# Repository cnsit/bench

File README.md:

# bench
An ideal bench design.
- [ ] Printer
- [ ] Copier & Scanner
- [ ] 3D Printer
- [ ] CNC
- [ ] Laser Cutter
- [ ] Power Supplies x2
- [ ] FT-991
- [ ] PC
- [ ] Mac
- [ ] Projector
- [ ] Stereo Audio
- [ ] 27 inch monitor
- [ ] Welding Station
- [ ] Tex 2465
- [ ] Curve Tracer
- [ ] Signal Generator x2
- [ ] Multimeter Holder x4
- [ ] Coax Cable holder
- [ ] No shadow lights
- [ ] Switch with serve nodes
- [ ] Antenna switch
- [ ] Optical

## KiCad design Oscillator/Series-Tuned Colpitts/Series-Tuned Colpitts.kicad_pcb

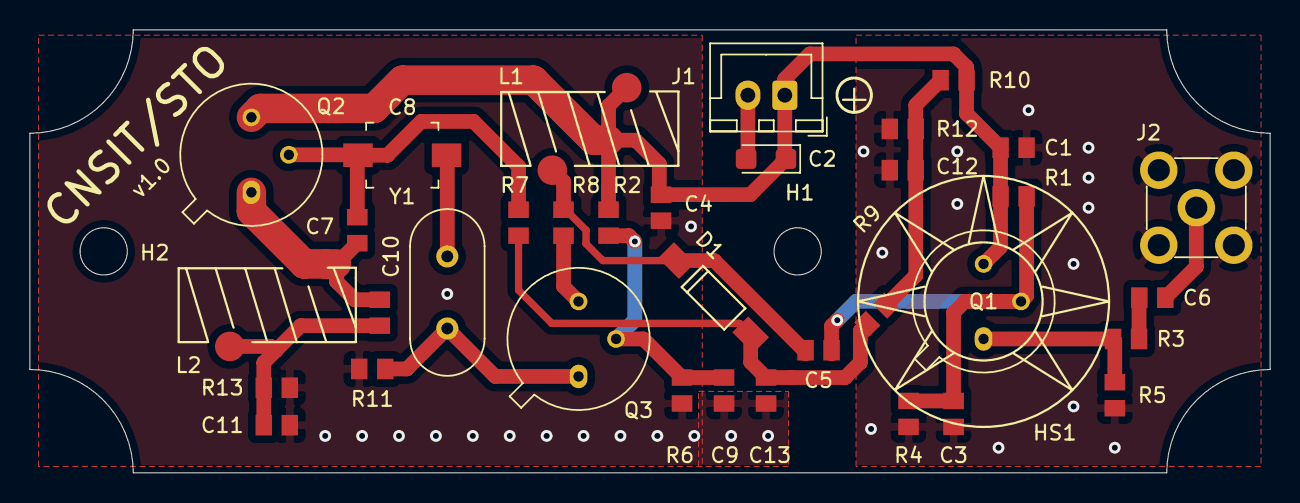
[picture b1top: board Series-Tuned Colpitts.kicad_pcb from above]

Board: 2 copper layers, 84.0 x 30.0 mm, 38 parts (0 on the bottom side), 16 nets.

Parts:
C1, C4, C6, C9, C11, C12, C13: 0.1u; C_0805_2012Metric
C2: 10u; CP_EIA-3216-10_Kemet-I
C3: 470p; C_0805_2012Metric
C5: 110p; C_0805_2012Metric
C7: 390p; C_0805_2012Metric
C8: 30p; C_Trimmer_Murata_TZB4-B
C10: 510p; C_0805_2012Metric
D1: 1N60; SMT_DIODE
H1, H2: MountingHole; MountingHole_3.2mm_M3
HS1: Heatsink; TO_39_Crown
J1: PWR; XH-A_1x02_Vertical_Power_In
J2: Out; SMA_Amphenol_901-144_Vertical
L1, L2: 4.3u; L_3743
Q1, Q2, Q3: 2N2219; TO-39-3
R1, R4: 10k; R_0805_2012Metric
R2: 6.8k; R_0805_2012Metric
R3: 470; R_0805_2012Metric
R5, R12, R13: 1k; R_0805_2012Metric
R6: 2.7k; R_0805_2012Metric
R7: 20k; R_0805_2012Metric
R8: 220; R_0805_2012Metric
R9: 33k; R_0805_2012Metric
R10: 1.5k; R_0805_2012Metric
R11: 270; R_0805_2012Metric
Y1: Crystal; Crystal_HC49-U_Vertical

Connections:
GND: C1.2, C2.2, C3.1, C4.2, C9.1, C11.2, C12.2, C13.2, J1.2, J2.2, R4.2, R5.2, R6.1, R11.2, R12.2, R13.2
unnamed: C1.1, C2.1, C4.1, J1.1, L1.1, Q1.3, Q2.3, R1.1, R2.1, R10.1
unnamed: C3.2, C5.1, Q1.2, R1.2, R4.1
unnamed: C5.2, D1.1, L1.2, R8.1
unnamed: C6.1, J2.1
unnamed: C6.2, R3.1
unnamed: C7.1, C8.1, Q2.2, R7.1
unnamed: C8.2, Y1.1
unnamed: C9.2, Q3.2, R2.2, R6.2
unnamed: C7.2, C10.1, L2.1, Q2.1
unnamed: C10.2, C11.1, L2.2, R13.1
unnamed: C12.1, R9.1, R10.2, R12.1
unnamed: C13.1, D1.2, R7.2, R9.2
unnamed: Q1.1, R3.2, R5.1
unnamed: Q3.1, R11.1, Y1.2
unnamed: Q3.3, R8.2

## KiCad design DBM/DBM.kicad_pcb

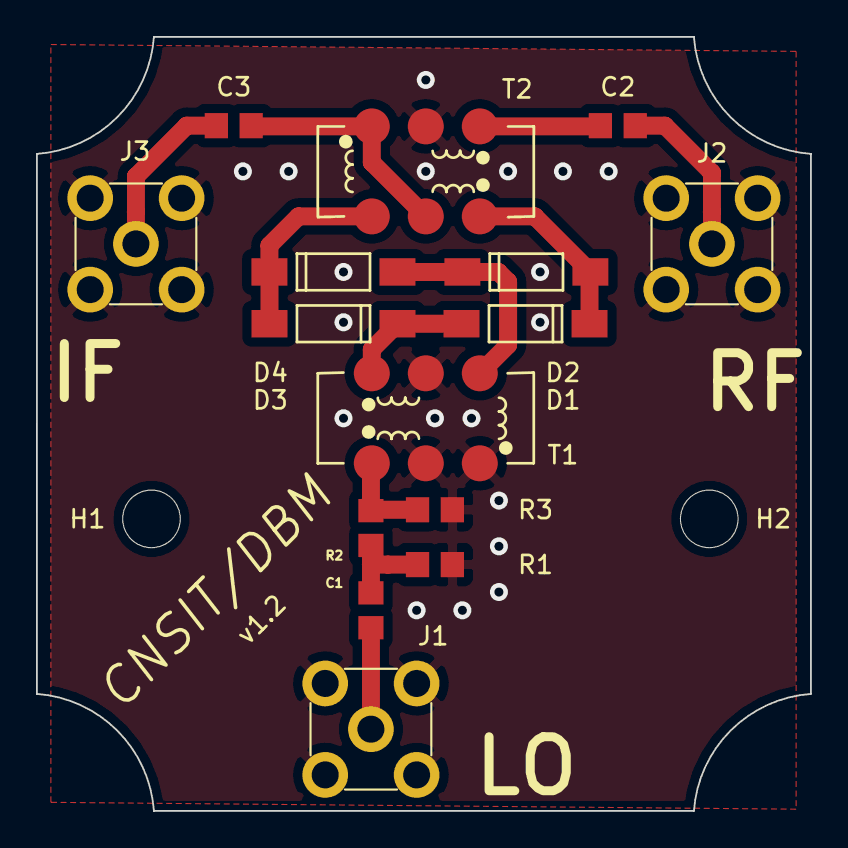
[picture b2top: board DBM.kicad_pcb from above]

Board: 2 copper layers, 43.0 x 43.0 mm, 17 parts (0 on the bottom side), 12 nets.

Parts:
C1, C2, C3: 0.1u; C_0805_2012Metric_Pad1.29x1.40mm_HandSolder
D1, D2, D3, D4: 1N60; SMT_DIODE
H1, H2: MountingHole; MountingHole_3.2mm_M3
J1: LO; SMA_Amphenol_901-144_Vertical
J2: RF; SMA_Amphenol_901-144_Vertical
J3: IF; SMA_Amphenol_901-144_Vertical
R1, R3: 150; R_0805_2012Metric_Pad1.29x1.40mm_HandSolder
R2: 37; R_0805_2012Metric_Pad1.29x1.40mm_HandSolder
T1, T2: T_3743; T_3743_6

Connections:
GNDA: J1.2, J2.2, J3.2, R1.2, R3.2, T1.2, T1.4, T1.5, T2.2
unnamed: C1.1, R1.1, R2.2
unnamed: C1.2, J1.1
unnamed: C2.1, T2.1
unnamed: C2.2, J2.1
unnamed: C3.1, J3.1
unnamed: C3.2, T2.4, T2.5
unnamed: D1.1, D2.2, T2.3
unnamed: D1.2, D3.1, T1.3
unnamed: D2.1, D4.2, T1.6
unnamed: D3.2, D4.1, T2.6
unnamed: R2.1, R3.1, T1.1

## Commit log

2020-02-27 本地基础版本签入
    包含 LCD 驱动以及可以运行的频率计和温度计。
2020-02-27 触摸屏
    可以初始化和触发中断
2020-02-27 触摸屏基本可用
    接下来需要进行校准测试以及对应UI的开发
2020-02-29 尝试各种字体
    FONT_APPLE_][_12PT 和 FONT_ENHANCED_DOT_DIGITAL_16PT 看起来比较舒服。
2020-03-06 重新布局 DBM PCB
    用了串联的二极管来提高动态范围
2020-03-06 准备打样
2020-03-10 加入串联谐振晶体振荡器电路
    FFT 初步框架。
